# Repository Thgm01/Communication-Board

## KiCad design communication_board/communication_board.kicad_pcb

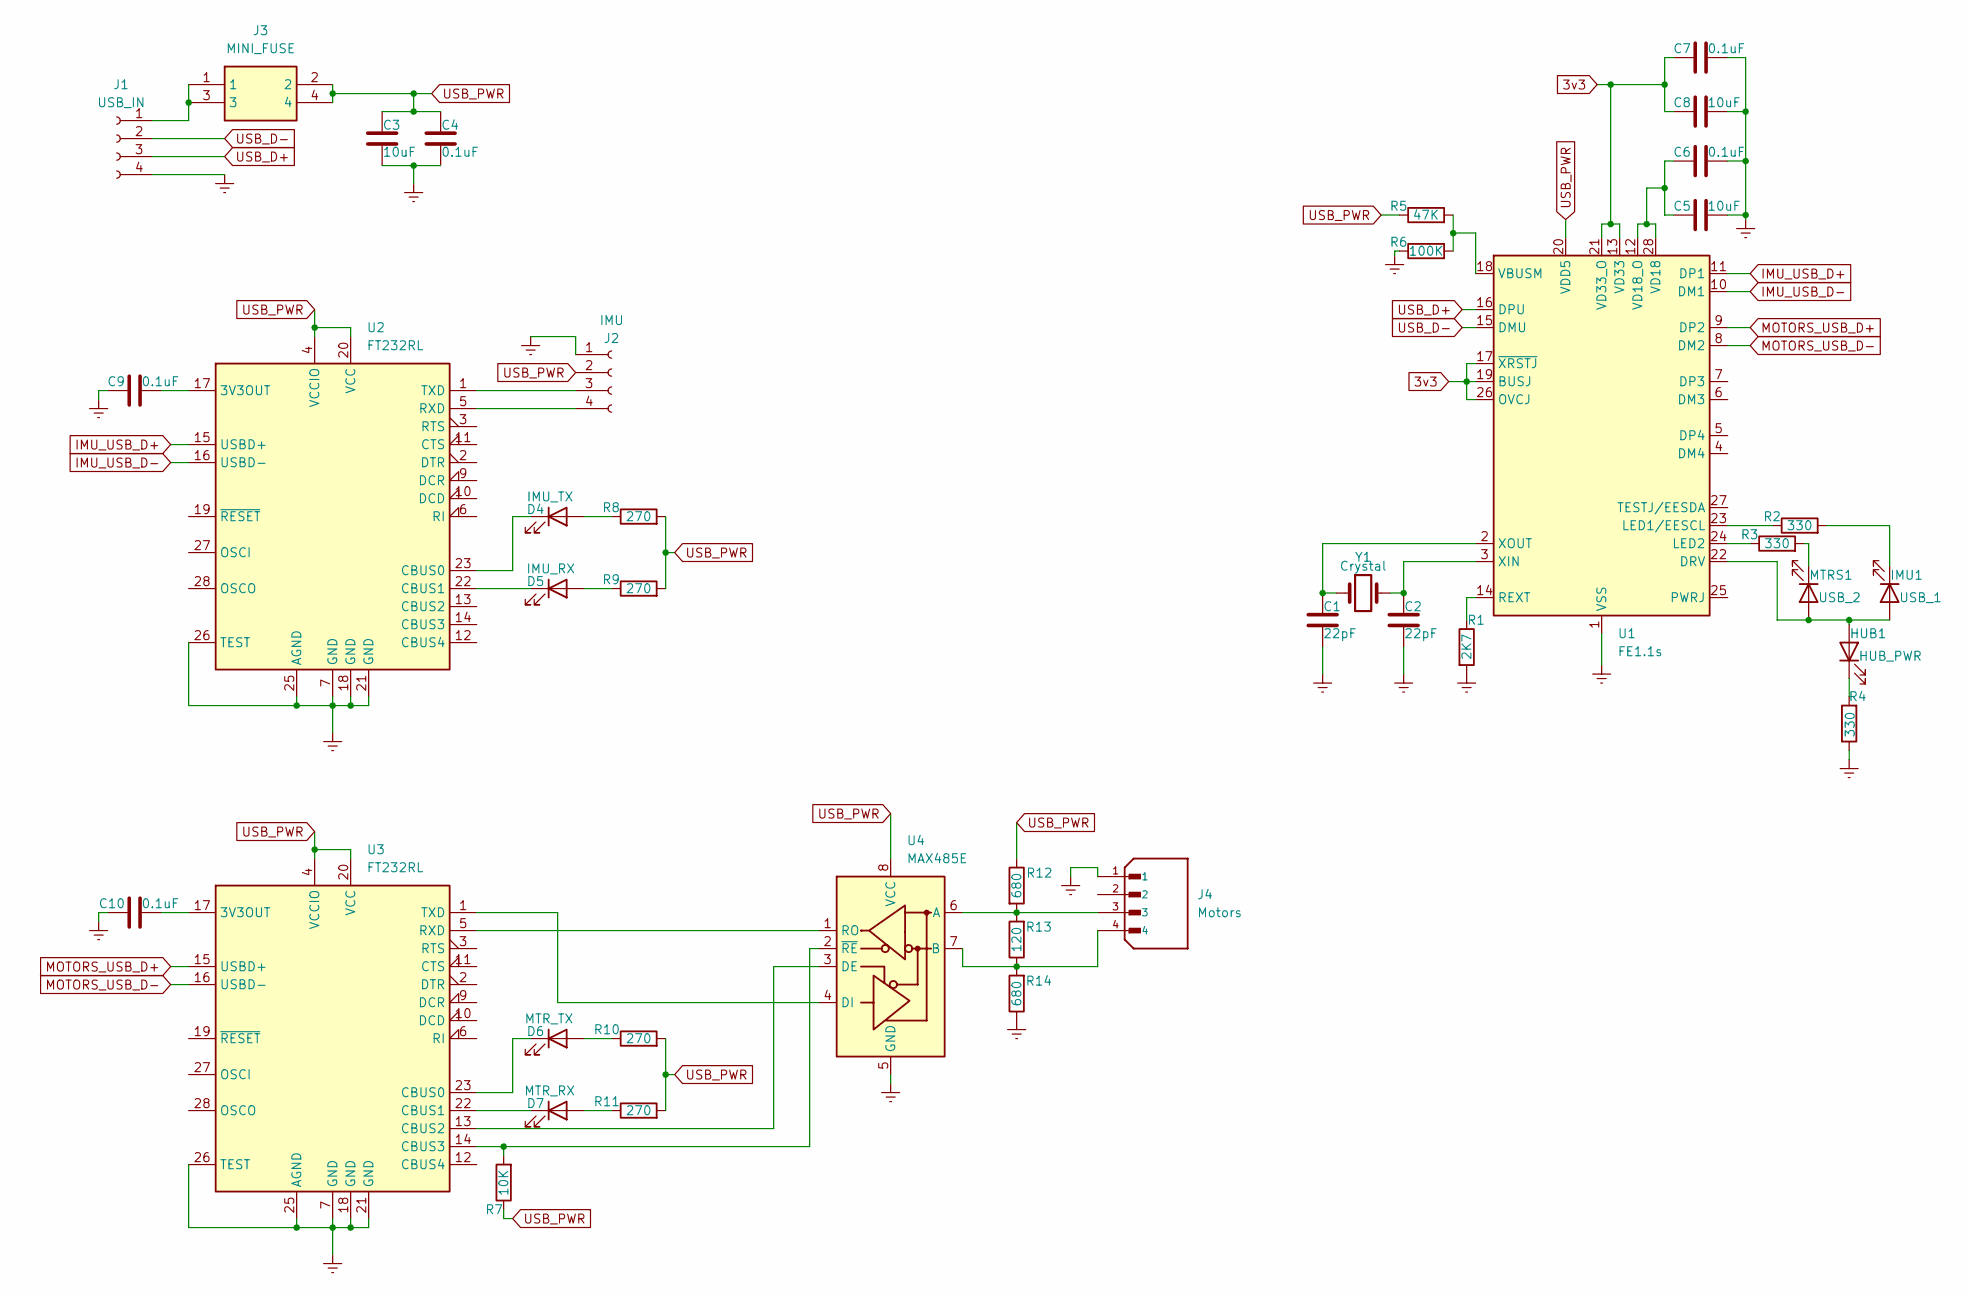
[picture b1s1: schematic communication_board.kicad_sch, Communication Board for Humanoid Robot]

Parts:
C1, C2: 22pF; C_1206_3216Metric
C3, C5, C8: 10uF; C_1206_3216Metric
C4, C6, C7, C9, C10: 0.1uF; C_1206_3216Metric
D4: IMU_TX; LED_1206_3216Metric_Pad1.42x1.75mm_HandSolder
D5: IMU_RX; LED_1206_3216Metric_Pad1.42x1.75mm_HandSolder
D6: MTR_TX; LED_1206_3216Metric_Pad1.42x1.75mm_HandSolder
D7: MTR_RX; LED_1206_3216Metric_Pad1.42x1.75mm_HandSolder
HUB1: HUB_PWR; LED_1206_3216Metric_Pad1.42x1.75mm_HandSolder
IMU1: USB_1; LED_1206_3216Metric_Pad1.42x1.75mm_HandSolder
J1: USB_IN; PinHeader_1x04_P2.54mm_Vertical
J2: IMU; PinHeader_1x04_P2.54mm_Vertical
J3: MINI_FUSE; Mouser Part Number 534-3557-2
J4: Motors; JST_EH_B4B-EH-A_1x04_P2.50mm_Vertical
MTRS1: USB_2; LED_1206_3216Metric_Pad1.42x1.75mm_HandSolder
R1: 2K7; R_1206_3216Metric
R2, R3, R4: 330; R_1206_3216Metric
R5: 47K; R_1206_3216Metric
R6: 100K; R_1206_3216Metric
R7: 10K; R_1206_3216Metric
R8, R9, R10, R11: 270; R_1206_3216Metric
R12, R14: 680; R_1206_3216Metric
R13: 120; R_1206_3216Metric
U1: FE1.1s; SSOP-28_3.9x9.9mm_P0.635mm
U2, U3: FT232RL; SSOP-28_5.3x10.2mm_P0.65mm
U4: MAX485E; SOIC-8_3.9x4.9mm_P1.27mm
Y1: Crystal; ECS120185PXGMTR

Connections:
3v3: C7.1, C8.1, U1.13 (VD33), U1.17 (~XRSTJ), U1.19 (BUSJ), U1.21 (VD33_O), U1.26 (OVCJ)
GNDREF: C1.2, C2.2, C3.2, C4.2, C5.2, C6.2, C7.2, C8.2, C9.1, C10.1, J1.4, J2.1, J4.1, R1.2, R4.1, R6.1, R14.1, U1.1 (VSS), U2.7 (GND), U2.18 (GND), U2.21 (GND), U2.25 (AGND), U2.26 (TEST), U3.7 (GND), U3.18 (GND), U3.21 (GND), U3.25 (AGND), U3.26 (TEST), U4.5 (GND)
IMU_USB_D+: U1.11 (DP1), U2.15 (USBD+)
IMU_USB_D-: U1.10 (DM1), U2.16 (USBD-)
MOTORS_USB_D+: U1.9 (DP2), U3.15 (USBD+)
MOTORS_USB_D-: U1.8 (DM2), U3.16 (USBD-)
unnamed: D4.2 (A), R8.1
unnamed: D4.1 (K), U2.23 (CBUS0)
unnamed: D5.2 (A), R9.1
unnamed: D5.1 (K), U2.22 (CBUS1)
unnamed: D6.2 (A), R10.1
unnamed: D6.1 (K), U3.23 (CBUS0)
unnamed: D7.2 (A), R11.1
unnamed: D7.1 (K), U3.22 (CBUS1)
unnamed: HUB1.2 (A), IMU1.2 (A), MTRS1.2 (A), U1.22 (DRV)
unnamed: HUB1.1 (K), R4.2
unnamed: IMU1.1 (K), R2.2
unnamed: J1.1, J3.1, J3.3
unnamed: J2.3, U2.1 (TXD)
unnamed: J2.4, U2.5 (RXD)
unnamed: MTRS1.1 (K), R3.2
unnamed: R2.1, U1.23 (LED1/EESCL)
unnamed: R3.1, U1.24 (LED2)
unnamed: R1.1, U1.14 (REXT)
unnamed: R5.2, R6.2, U1.18 (VBUSM)
unnamed: C5.1, C6.1, U1.12 (VD18_O), U1.28 (VD18)
unnamed: C2.1, U1.3 (XIN), Y1.2
unnamed: C1.1, U1.2 (XOUT), Y1.1
unnamed: C9.2, U2.17 (3V3OUT)
unnamed: C10.2, U3.17 (3V3OUT)
unnamed: U3.13 (CBUS2), U4.3 (DE)
unnamed: R7.2, U3.14 (CBUS3), U4.2 (~RE)
unnamed: U3.5 (RXD), U4.1 (RO)
unnamed: U3.1 (TXD), U4.4 (DI)
unnamed: J4.3, R12.2, R13.2, U4.6 (A)
unnamed: J4.4, R13.1, R14.2, U4.7 (B)
USB_D+: J1.3, U1.16 (DPU)
USB_D-: J1.2, U1.15 (DMU)
USB_PWR: C3.1, C4.1, J2.2, J3.2, J3.4, R5.1, R7.1, R8.2, R9.2, R10.2, R11.2, R12.1, U1.20 (VDD5), U2.4 (VCCIO), U2.20 (VCC), U3.4 (VCCIO), U3.20 (VCC), U4.8 (VCC)

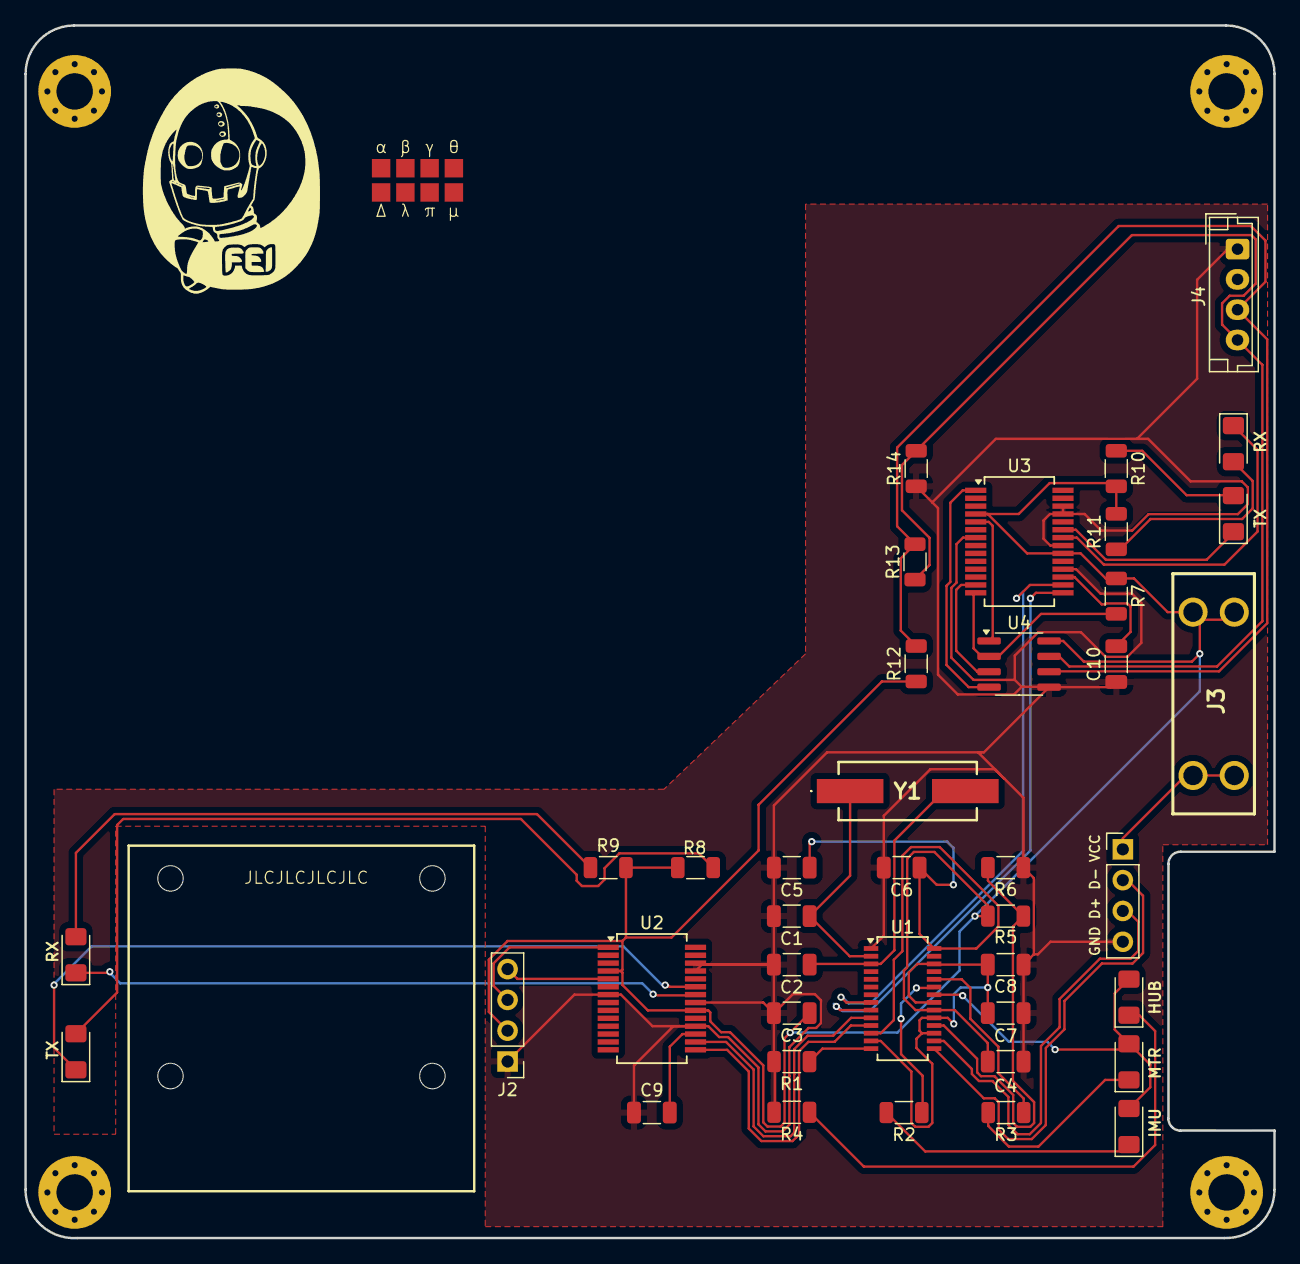
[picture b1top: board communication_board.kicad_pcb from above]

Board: 2 copper layers, 103.0 x 100.0 mm, 40 parts (0 on the bottom side), 39 nets.

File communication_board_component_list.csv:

"Reference","Value","Datasheet","Footprint","Qty","DNP"
"C1,C2","22pF","~","Capacitor_SMD:C_1206_3216Metric","2",""
"C3,C5,C8","10uF","~","Capacitor_SMD:C_1206_3216Metric","3",""
"C4,C6,C7,C9,C10","0.1uF","~","Capacitor_SMD:C_1206_3216Metric","5",""
"D4","IMU_TX","~","LED_SMD:LED_1206_3216Metric_Pad1.42x1.75mm_HandSolder","1",""
"D5","IMU_RX","~","LED_SMD:LED_1206_3216Metric_Pad1.42x1.75mm_HandSolder","1",""
"D6","MTR_TX","~","LED_SMD:LED_1206_3216Metric_Pad1.42x1.75mm_HandSolder","1",""
"D7","MTR_RX","~","LED_SMD:LED_1206_3216Metric_Pad1.42x1.75mm_HandSolder","1",""
"HUB1","HUB_PWR","~","LED_SMD:LED_1206_3216Metric_Pad1.42x1.75mm_HandSolder","1",""
"IMU1","USB_1","~","LED_SMD:LED_1206_3216Metric_Pad1.42x1.75mm_HandSolder","1",""
"J1","USB_IN","~","Connector_PinHeader_2.54mm:PinHeader_1x04_P2.54mm_Vertical","1",""
"J2","IMU","~","Connector_PinHeader_2.54mm:PinHeader_1x04_P2.54mm_Vertical","1",""
"J3","MINI_FUSE","http://www.keyelco.com/product-pdf.cfm?p=296","humanoid:MINI_FUSE","1",""
"J4","Motors","","Connector_JST:JST_EH_B4B-EH-A_1x04_P2.50mm_Vertical","1",""
"MTRS1","USB_2","~","LED_SMD:LED_1206_3216Metric_Pad1.42x1.75mm_HandSolder","1",""
"R1","2K7","~","Resistor_SMD:R_1206_3216Metric","1",""
"R2,R3,R4","330","~","Resistor_SMD:R_1206_3216Metric","3",""
"R5","47K","~","Resistor_SMD:R_1206_3216Metric","1",""
"R6","100K","~","Resistor_SMD:R_1206_3216Metric","1",""
"R7","10K","~","Resistor_SMD:R_1206_3216Metric","1",""
"R8,R9,R10,R11","270","~","Resistor_SMD:R_1206_3216Metric","4",""
"R12,R14","680","~","Resistor_SMD:R_1206_3216Metric","2",""
"R13","120","~","Resistor_SMD:R_1206_3216Metric","1",""
"U1","FE1.1s","https://cdn-shop.adafruit.com/product-files/2991/FE1.1s+Data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","Package_SO:SSOP-28_3.9x9.9mm_P0.635mm","1",""
"U2,U3","FT232RL","https://www.ftdichip.com/Support/Documents/DataSheets/ICs/DS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","Package_SO:SSOP-28_5.3x10.2mm_P0.65mm","2",""
"U4","MAX485E","https://datasheets.maximintegrated.com/en/ds/MAX1487E-MAX491E.pdf","Package_SO:SOIC-8_3.9x4.9mm_P1.27mm","1",""
"Y1","Crystal","~","components:ECS120185PXGMTR","1",""

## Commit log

2024-07-07 hub and imu tested at the same time
2024-07-07 motors conversor almost ready for test
2024-07-10 initial pcd components disposition
2024-07-12 start to track
2024-07-12 board cut ajusted
2024-07-12 communication board finished
2024-08-21 board with imu holes
2024-08-23 Lista de materiais e plano terra
2024-08-27 pequenas mudanças
2024-08-28 crianddo Biblioteca do Humanoid correta
2024-08-29 mudancas finais
